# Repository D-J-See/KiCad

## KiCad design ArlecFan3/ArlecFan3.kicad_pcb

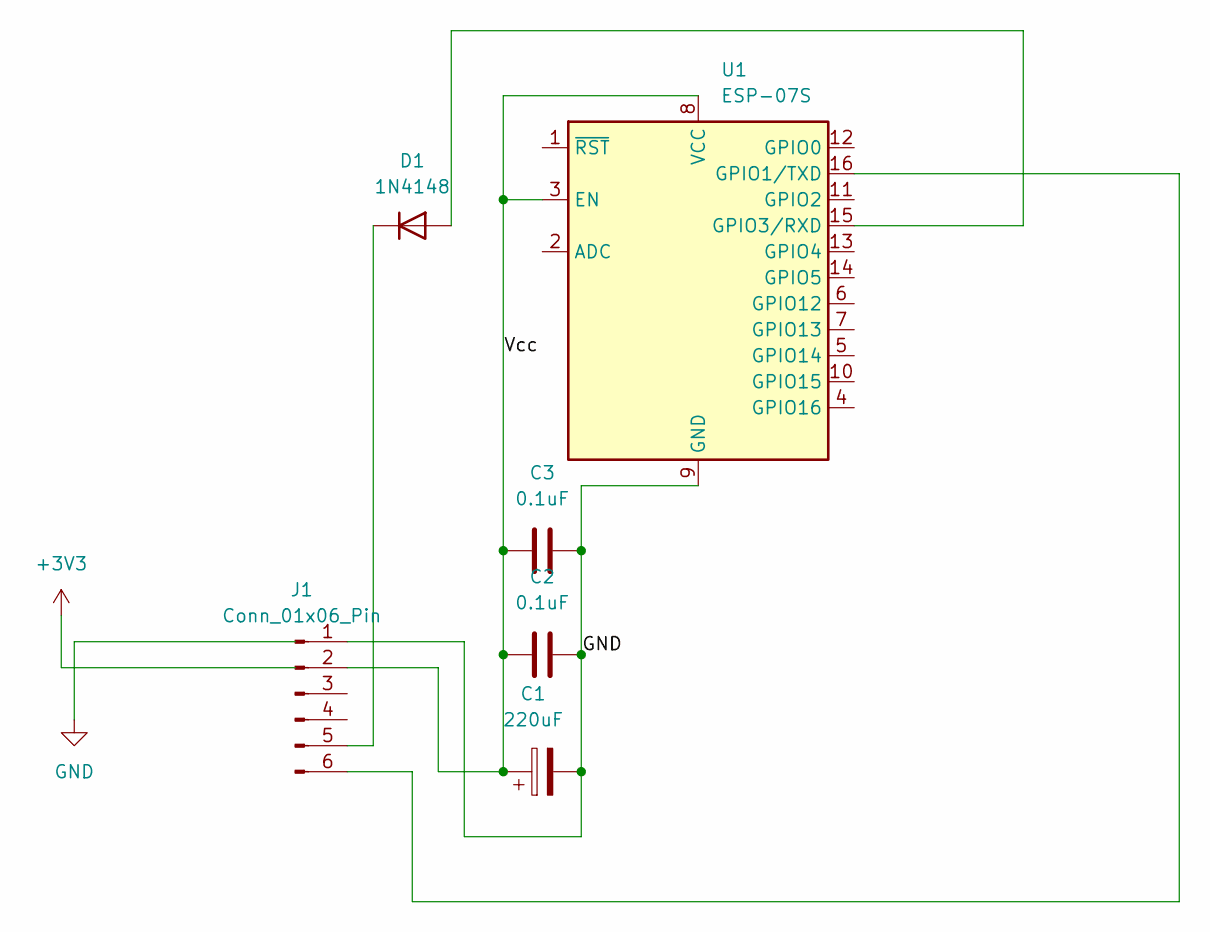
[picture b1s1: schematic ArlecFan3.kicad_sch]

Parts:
C1: 220uF; CP_Radial_D6.3mm_P2.50mm
C2, C3: 0.1uF; C_0805_2012Metric_Pad1.18x1.45mm_HandSolder
D1: 1N4148; D_0805_2012Metric_Pad1.15x1.40mm_HandSolder
J1: Conn_01x06_Pin; PinHeader_1x06_P2.00mm_Vertical
U1: ESP-07S

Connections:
/Vcc: C1.1, C2.1, C3.1, J1.2, U1.3 (EN), U1.8 (VCC)
GND: C1.2, C2.2, C3.2, J1.1, U1.9 (GND)
unnamed: D1.2 (A), U1.15 (GPIO3/RXD)
unnamed: D1.1 (K), J1.5
unnamed: J1.6, U1.16 (GPIO1/TXD)

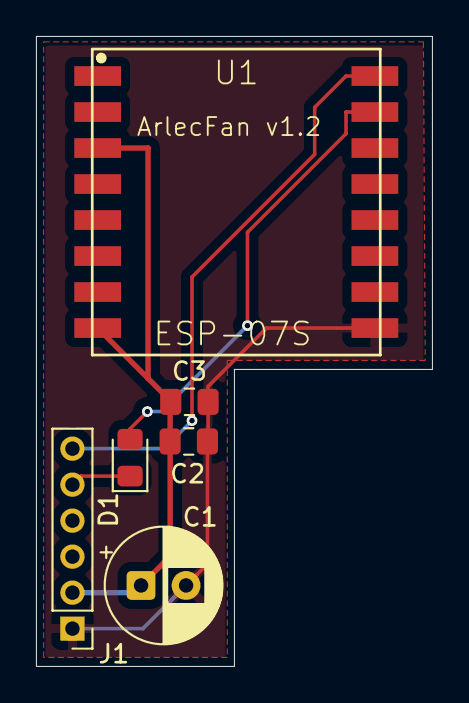
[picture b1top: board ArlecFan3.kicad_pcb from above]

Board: 2 copper layers, 22.0 x 35.0 mm, 6 parts (0 on the bottom side), 5 nets.

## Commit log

2025-12-15 Add ArlecFan
